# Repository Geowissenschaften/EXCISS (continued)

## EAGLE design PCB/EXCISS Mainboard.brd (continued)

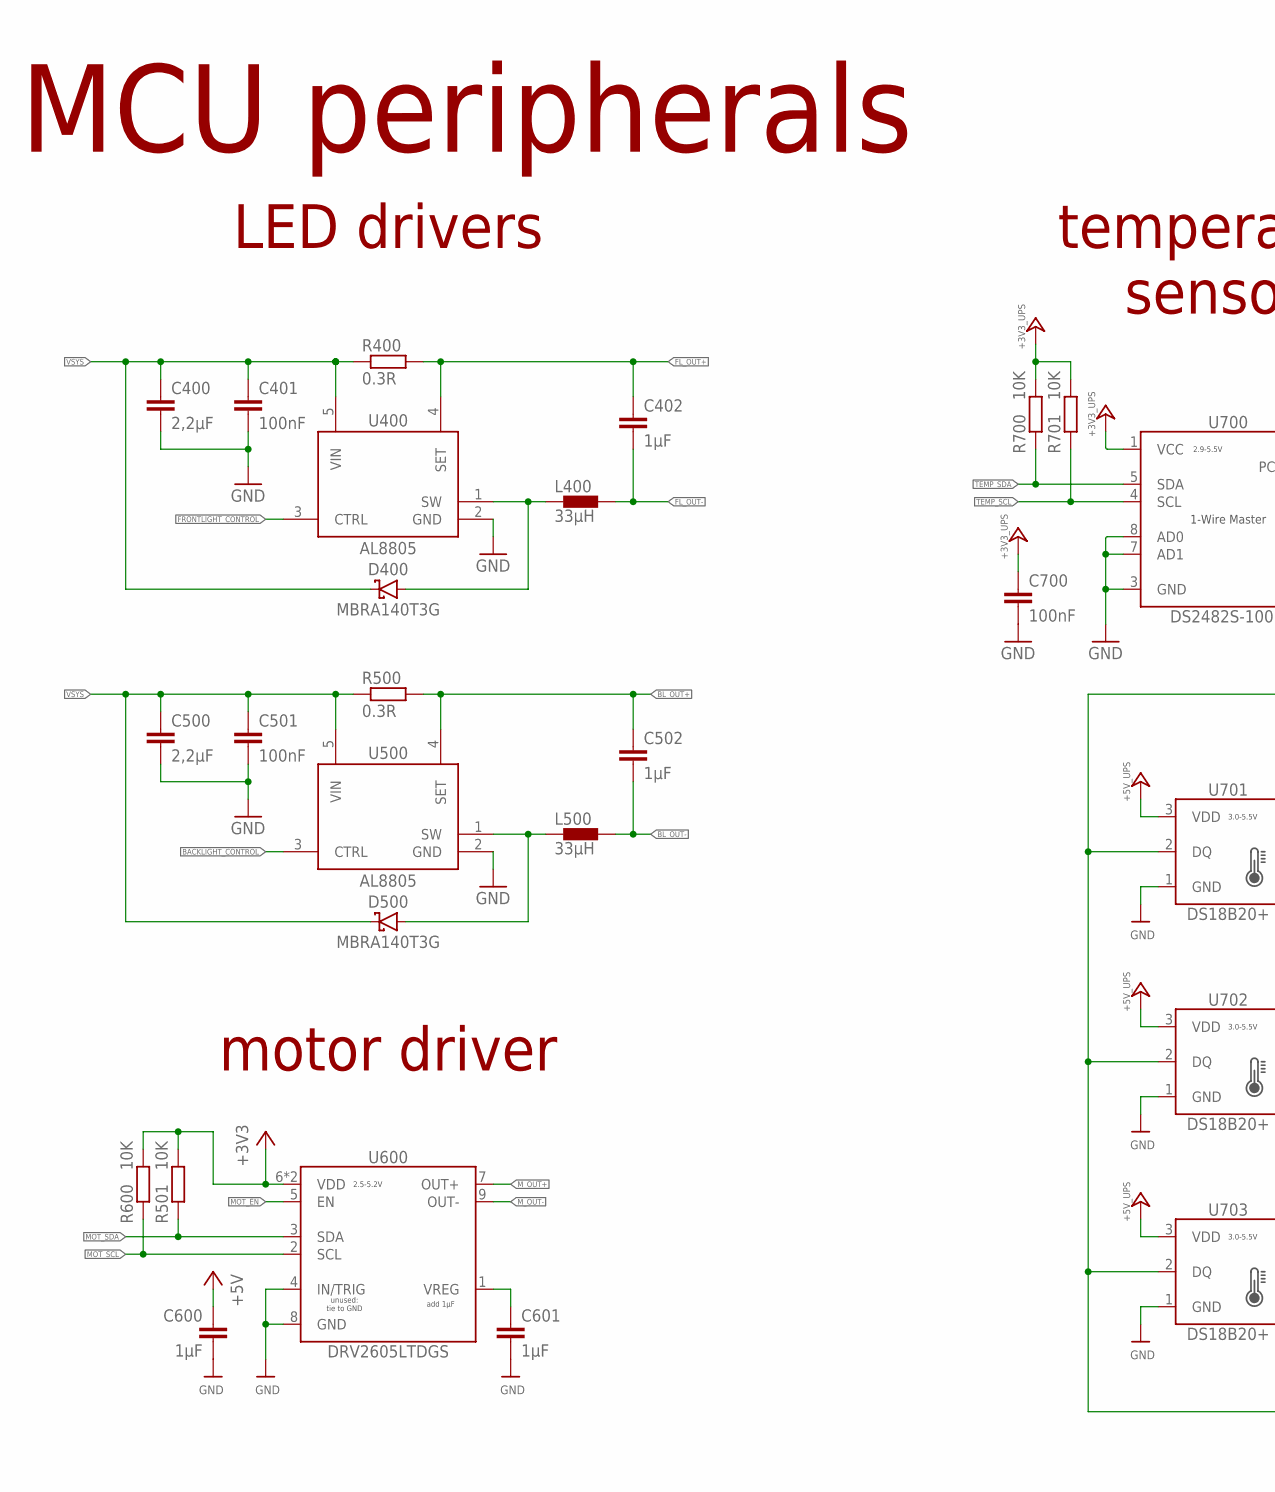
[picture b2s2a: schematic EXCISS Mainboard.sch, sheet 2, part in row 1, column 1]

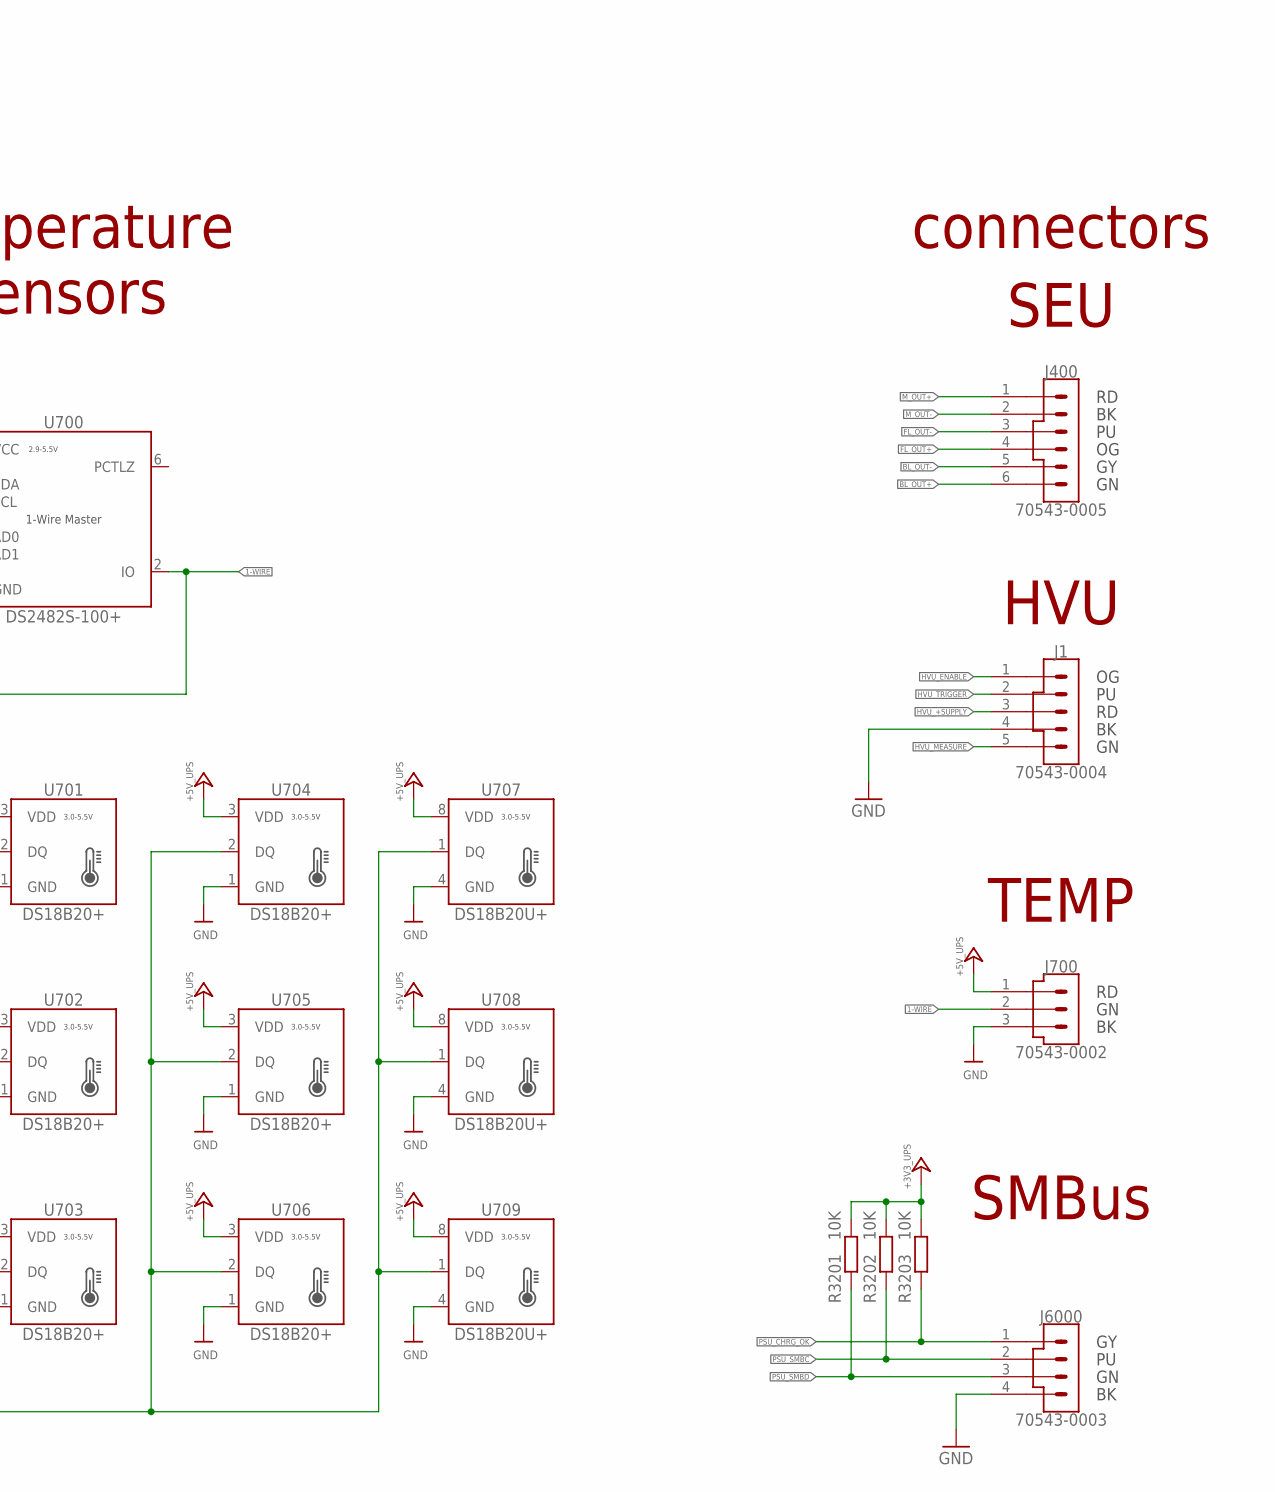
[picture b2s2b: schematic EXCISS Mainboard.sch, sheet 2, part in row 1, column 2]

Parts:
C400, C500: 2,2µF; C1206
C401, C501: 100nF; C0805
C402, C502, C600, C601: 1µF; C0805
C700: 100nF; C0603
D400, D500: MBRA140T3G; 403D-02
J1: 70543-0004; MOLEX_70543-0004
J400: 70543-0005; MOLEX_70543-0005
J700: 70543-0002; MOLEX_70543-0002
J6000: 70543-0003; MOLEX_70543-0003
L400, L500: 33µH; SRN6045
R400, R500: 0.3R; R0805
R501, R600, R700, R701, R3201, R3202, R3203: 10K; R0603
U400, U500: AL8805; DBV(R-PDSO-G5)
U600: DRV2605LTDGS; PSOP10
U700: DS2482S-100+; SOIC8
U701, U702, U703, U704, U705, U706: DS18B20+; TO-92-STRAIGHT
U707, U708, U709: DS18B20U+; µSOP

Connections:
1-WIRE: J700.2, U700.2 (IO), U701.2 (DQ), U702.2 (DQ), U703.2 (DQ), U704.2 (DQ), U705.2 (DQ), U706.2 (DQ), U707.1 (DQ), U708.1 (DQ), U709.1 (DQ)
+3V3: C600.1, R501.1, R600.1, U600.6 (VDD), U600.10 (VDD); also elsewhere on the board
+3V3_UPS: C700.1, R700.1, R701.1, R3201.1, R3202.1, R3203.1, U700.1 (VCC); also elsewhere on the board
+5V_UPS: J700.1, U701.3 (VDD), U702.3 (VDD), U703.3 (VDD), U704.3 (VDD), U705.3 (VDD), U706.3 (VDD), U707.8 (VDD), U708.8 (VDD), U709.8 (VDD); also elsewhere on the board
BACKLIGHT_CONTROL: U500.3 (CTRL); also elsewhere on the board
BL_OUT+: C502.1, J400.6, R500.2, U500.4 (SET)
BL_OUT-: C502.2, J400.5, L500.2
BL_SW: D500.A, L500.1, U500.1 (SW)
FL_OUT+: C402.1, J400.4, R400.2, U400.4 (SET)
FL_OUT-: C402.2, J400.3, L400.2
FL_SW: D400.A, L400.1, U400.1 (SW)
FRONTLIGHT_CONTROL: U400.3 (CTRL); also elsewhere on the board
GND: C400.2, C401.2, C500.2, C501.2, C600.2, C601.2, C700.2, J1.4, J700.3, J6000.4, U400.2 (GND), U500.2 (GND), U600.4 (IN/TRIG), U600.8 (GND), U700.3 (GND), U700.7 (AD1), U700.8 (AD0), U701.1 (GND), U702.1 (GND), U703.1 (GND), U704.1 (GND), U705.1 (GND), U706.1 (GND), U707.4 (GND), U708.4 (GND), U709.4 (GND); also elsewhere on the board
HVU_+SUPPLY: J1.3; also elsewhere on the board
HVU_ENABLE: J1.1; also elsewhere on the board
HVU_MEASURE: J1.5; also elsewhere on the board
HVU_TRIGGER: J1.2; also elsewhere on the board
MOT_!EN: U600.5 (EN); also elsewhere on the board
MOT_SCL: R600.2, U600.2 (SCL); also elsewhere on the board
MOT_SDA: R501.2, U600.3 (SDA); also elsewhere on the board
M_OUT+: J400.1, U600.7 (OUT+)
M_OUT-: J400.2, U600.9 (OUT-)
unnamed: C601.1, U600.1 (VREG)
PSU_CHRG_OK: J6000.1, R3203.2; also elsewhere on the board
PSU_SMBC: J6000.2, R3202.2; also elsewhere on the board
PSU_SMBD: J6000.3, R3201.2; also elsewhere on the board
TEMP_SCL: R701.2, U700.4 (SCL); also elsewhere on the board
TEMP_SDA: R700.2, U700.5 (SDA); also elsewhere on the board
VSYS: C400.1, C401.1, C500.1, C501.1, D400.C, D500.C, R400.1, R500.1, U400.5 (VIN), U500.5 (VIN); also elsewhere on the board

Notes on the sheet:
MCU peripherals
LED drivers
motor driver
temperature sensors
connectors
SEU
TEMP
HVU
SMBus

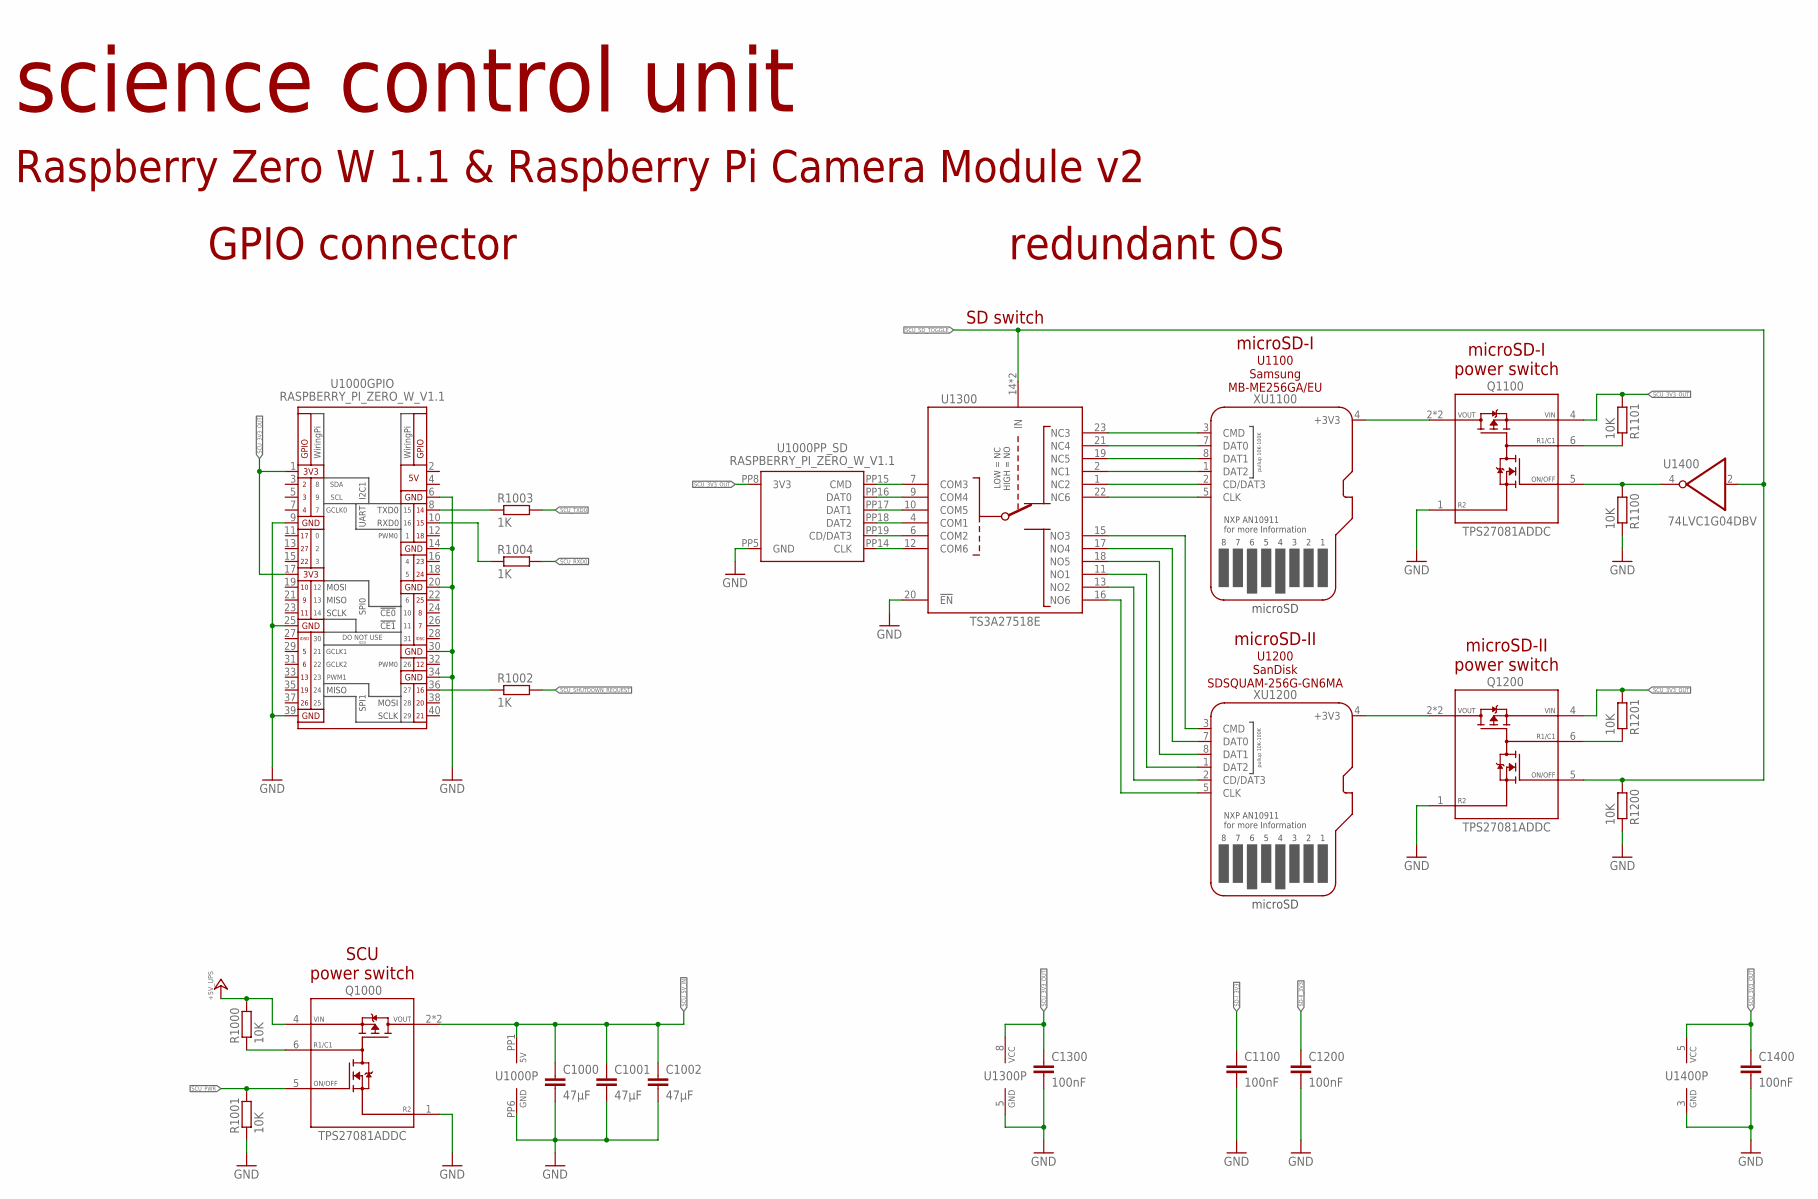
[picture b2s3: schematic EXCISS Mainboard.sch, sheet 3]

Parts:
C1000, C1001, C1002: 47µF; C1210
C1100, C1200, C1300, C1400: 100nF; C0603
Q1000, Q1100, Q1200: TPS27081ADDC; DDC(R-PDSO-G6)
R1000, R1001, R1100, R1101, R1200, R1201: 10K; R0603
R1002, R1003, R1004: 1K; R0603
U1000: RASPBERRY_PI_ZERO_W_V1.1
U1300: TS3A27518E; TSSOP24
U1400: 74LVC1G04DBV; DBV(R-PDSO-G5)
XU1100, XU1200: MICROSDMOLEX_104031; MICROSD_MOLEX_104031

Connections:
+5V_UPS: Q1000.4 (VIN), R1000.2; also elsewhere on the board
GND: C1000.2, C1001.2, C1002.2, C1100.2, C1200.2, C1300.2, C1400.2, Q1000.1 (R2), Q1100.1 (R2), Q1200.1 (R2), R1001.1, R1100.1, R1200.1, U1000.6 (GND), U1000.9 (GND), U1000.14 (GND), U1000.20 (GND), U1000.25 (GND), U1000.30 (GND), U1000.34 (GND), U1000.39 (GND), U1000.PP5 (GND), U1000.PP6 (GND), U1300.5 (GND), U1300.20 (!EN), U1400.3 (GND), XU1100.6 (GND), XU1100.G1 (GND), XU1100.G2 (GND), XU1100.G3 (GND), XU1100.G4 (GND), XU1200.6 (GND), XU1200.G1 (GND), XU1200.G2 (GND), XU1200.G3 (GND), XU1200.G4 (GND); also elsewhere on the board
unnamed: U1000.PP15 (CMD), U1300.7 (COM3)
unnamed: U1000.PP16 (DAT0), U1300.9 (COM4)
unnamed: U1000.PP14 (CLK), U1300.12 (COM6)
unnamed: U1000.PP19 (CD/DAT3), U1300.6 (COM2)
unnamed: U1000.PP18 (DAT2), U1300.4 (COM1)
unnamed: U1000.PP17 (DAT1), U1300.10 (COM5)
unnamed: R1002.1, U1000.36 (GPIO16)
unnamed: R1004.1, U1000.10 (GPIO15/RXD0)
unnamed: R1003.1, U1000.8 (GPIO14/TXD0)
R1/C1: Q1100.6 (R1/C1), R1101.1
R1/C2: Q1200.6 (R1/C1), R1201.1
R1/C6: Q1000.6 (R1/C1), R1000.1
SCU_3V3_OUT: C1300.1, C1400.1, Q1100.4 (VIN), Q1200.4 (VIN), R1101.2, R1201.2, U1000.1 (3V3), U1000.17 (3V3), U1000.PP8 (3V3), U1300.8 (VCC), U1400.5 (VCC)
SCU_5V_IN: C1000.1, C1001.1, C1002.1, Q1000.2 (VOUT), Q1000.3 (VOUT), U1000.PP1 (5V)
SCU_PWR: Q1000.5 (ON/OFF), R1001.2; also elsewhere on the board
SCU_RXD0: R1004.2; also elsewhere on the board
SCU_SD_!TOGGLE: Q1100.5 (ON/OFF), R1100.2, U1400.4 (O)
SCU_SD_TOGGLE: Q1200.5 (ON/OFF), R1200.2, U1300.14 (IN), U1300.24 (IN), U1400.2 (I); also elsewhere on the board
SCU_SHUTDOWN_REQUEST: R1002.2; also elsewhere on the board
SCU_TXD0: R1003.2; also elsewhere on the board
SD-1_CD/DAT3: U1300.1 (NC2), XU1100.2 (CD/DAT3)
SD-1_CLK: U1300.22 (NC6), XU1100.5 (CLK)
SD-1_CMD: U1300.23 (NC3), XU1100.3 (CMD)
SD-1_DAT0: U1300.21 (NC4), XU1100.7 (DAT0)
SD-1_DAT1: U1300.19 (NC5), XU1100.8 (DAT1)
SD-1_DAT2: U1300.2 (NC1), XU1100.1 (DAT2)
SD-2_CD/DAT3: U1300.13 (NO2), XU1200.2 (CD/DAT3)
SD-2_CLK: U1300.16 (NO6), XU1200.5 (CLK)
SD-2_CMD: U1300.15 (NO3), XU1200.3 (CMD)
SD-2_DAT0: U1300.17 (NO4), XU1200.7 (DAT0)
SD-2_DAT1: U1300.18 (NO5), XU1200.8 (DAT1)
SD-2_DAT2: U1300.11 (NO1), XU1200.1 (DAT2)
SD-II_3V3: C1200.1, Q1200.2 (VOUT), Q1200.3 (VOUT), XU1200.4 (+3V3)
SD-I_3V3: C1100.1, Q1100.2 (VOUT), Q1100.3 (VOUT), XU1100.4 (+3V3)

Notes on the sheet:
science control unit
GPIO connector
redundant OS
microSD-I power switch
microSD-II power switch
SCU power switch
Raspberry Zero W 1.1 & Raspberry Pi Camera Module v2
microSD-I
microSD-II
SD switch
U1100 Samsung MB-ME256GA/EU
U1200 SanDisk SDSQUAM-256G-GN6MA

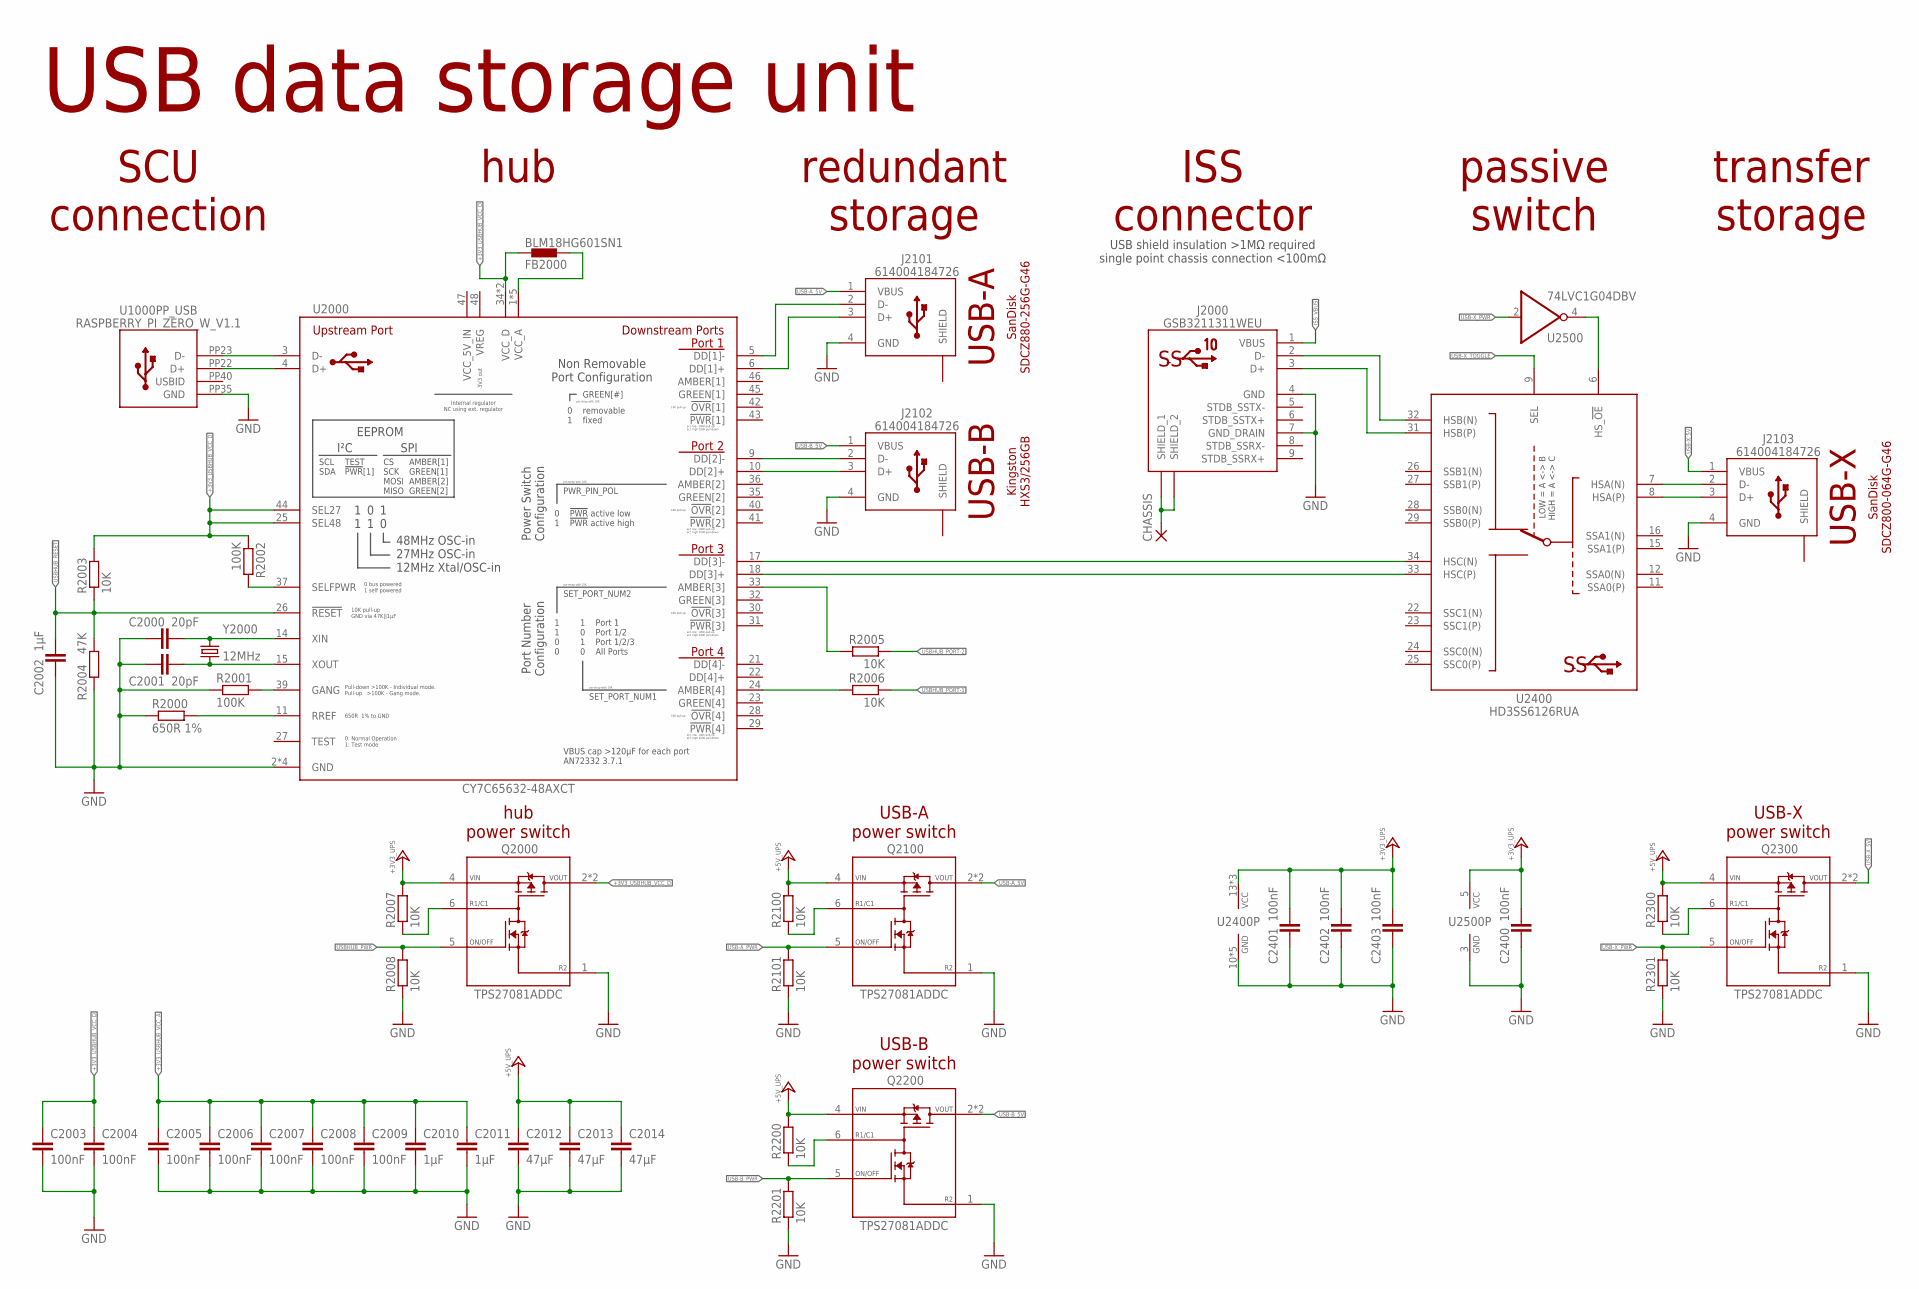
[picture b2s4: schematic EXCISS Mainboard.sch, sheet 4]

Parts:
C2000, C2001: 20pF; C0603
C2002, C2010, C2011: 1µF; C0805
C2003, C2004, C2005, C2006, C2007, C2008, C2009, C2400, C2401, C2402, C2403: 100nF; C0603
C2012, C2013, C2014: 47µF; C1210
CHASSIS: PAD_M2.5
FB2000: BLM18HG601SN1; 0603
J2000: GSB3211311WEU
J2101, J2102, J2103: 614004184726
Q2000, Q2100, Q2200, Q2300: TPS27081ADDC; DDC(R-PDSO-G6)
R2000: 650R 1%; R0603
R2001, R2002: 100K; R0603
R2003, R2005, R2006, R2007, R2008, R2100, R2101, R2200, R2201, R2300, R2301: 10K; R0603
R2004: 47K; R0603
U1000: RASPBERRY_PI_ZERO_W_V1.1
U2000: CY7C65632-48AXCT; TQFP48
U2400: HD3SS6126RUA; RUA(R-PWQFN-N42)
U2500: 74LVC1G04DBV; DBV(R-PDSO-G5)
Y2000: 12MHz; HC49UP

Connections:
+3V3_UPS: C2400.1, C2401.1, C2402.1, C2403.1, Q2000.4 (VIN), R2007.2, U2400.13 (VCC), U2400.20 (VCC), U2400.30 (VCC), U2500.5 (VCC); also elsewhere on the board
+3V3_USBHUB_VCC_A: C2005.1, C2006.1, C2007.1, C2008.1, C2009.1, C2010.1, C2011.1, FB2000.2, U2000.1 (VCC_A), U2000.7 (VCC_A), U2000.12 (VCC_A), U2000.16 (VCC_A), U2000.19 (VCC_A)
+3V3_USBHUB_VCC_D: C2003.1, C2004.1, FB2000.1, Q2000.2 (VOUT), Q2000.3 (VOUT), R2002.1, R2003.2, U2000.25 (SEL48), U2000.34 (VCC_D), U2000.38 (VCC_D), U2000.44 (SEL27)
+5V_UPS: C2012.1, C2013.1, C2014.1, Q2100.4 (VIN), Q2200.4 (VIN), Q2300.4 (VIN), R2100.2, R2200.2, R2300.2; also elsewhere on the board
DD[1]_N: J2101.2 (D-), U2000.5 (DD[1]-)
DD[1]_P: J2101.3 (D+), U2000.6 (DD[1]+)
DD[2]_N: J2102.2 (D-), U2000.9 (DD[2]-)
DD[2]_P: J2102.3 (D+), U2000.10 (DD[2]+)
DD[3]_N: U2000.17 (DD[3]-), U2400.34 (HSC(N))
DD[3]_P: U2000.18 (DD[3]+), U2400.33 (HSC(P))
DU_N: U1000.PP23 (D-), U2000.3 (D-)
DU_P: U1000.PP22 (D+), U2000.4 (D+)
GND: C2000.2, C2001.2, C2002.2, C2003.2, C2004.2, C2005.2, C2006.2, C2007.2, C2008.2, C2009.2, C2010.2, C2011.2, C2012.2, C2013.2, C2014.2, C2400.2, C2401.2, C2402.2, C2403.2, J2000.4 (GND), J2000.7 (GND_DRAIN), J2101.4 (GND), J2102.4 (GND), J2103.4 (GND), Q2000.1 (R2), Q2100.1 (R2), Q2200.1 (R2), Q2300.1 (R2), R2000.1, R2001.1, R2004.1, R2008.1, R2101.1, R2201.1, R2301.1, U1000.PP35 (GND), U2000.2 (GND), U2000.8 (GND), U2000.13 (GND), U2000.20 (GND), U2400.10 (GND), U2400.14 (GND), U2400.17 (GND), U2400.19 (GND), U2400.21 (GND), U2400.TP0 (GND), U2400.TP1 (GND), U2400.TP2 (GND), U2400.TP3 (GND), U2400.TP4 (GND), U2400.TP5 (GND), U2400.TP6 (GND), U2400.TP7 (GND), U2400.TP8 (GND), U2400.TP9 (GND), U2400.TP10 (GND), U2400.TP11 (GND), U2400.TP12 (GND), U2400.TP13 (GND), U2400.TP14 (GND), U2500.3 (GND); also elsewhere on the board
ISS_VBUS: J2000.1 (VBUS); also elsewhere on the board
unnamed: CHASSIS.P$1, J2000.SHIELD_1, J2000.SHIELD_2
unnamed: Q2100.6 (R1/C1), R2100.1
unnamed: R2001.2, U2000.39 (GANG)
unnamed: C2000.1, U2000.14 (XIN), Y2000.1
unnamed: C2001.1, U2000.15 (XOUT), Y2000.2
unnamed: R2006.2, U2000.24 (AMBER[4])
unnamed: R2005.2, U2000.33 (AMBER[3])
unnamed: R2000.2, U2000.11 (RREF)
unnamed: R2002.2, U2000.37 (SELFPWR)
R1/C3: Q2000.6 (R1/C1), R2007.1
R1/C4: Q2200.6 (R1/C1), R2200.1
R1/C5: Q2300.6 (R1/C1), R2300.1
USB-A_5V: J2101.1 (VBUS), Q2100.2 (VOUT), Q2100.3 (VOUT)
USB-A_PWR: Q2100.5 (ON/OFF), R2101.2; also elsewhere on the board
USB-B_5V: J2102.1 (VBUS), Q2200.2 (VOUT), Q2200.3 (VOUT)
USB-B_PWR: Q2200.5 (ON/OFF), R2201.2; also elsewhere on the board
USB-X_5V: J2103.1 (VBUS), Q2300.2 (VOUT), Q2300.3 (VOUT)
USB-X_!PWR: U2400.6 (HS_!OE), U2500.4 (O)
USB-X_PWR: Q2300.5 (ON/OFF), R2301.2, U2500.2 (I); also elsewhere on the board
USB-X_TOGGLE: U2400.9 (SEL); also elsewhere on the board
USBHUB_!RESET: C2002.1, R2003.1, R2004.2, U2000.26 (!RESET); also elsewhere on the board
USBHUB_PORT-1: R2006.1; also elsewhere on the board
USBHUB_PORT-2: R2005.1; also elsewhere on the board
USBHUB_PWR: Q2000.5 (ON/OFF), R2008.2; also elsewhere on the board
USBISS_D_N: J2000.2 (D-), U2400.32 (HSB(N))
USBISS_D_P: J2000.3 (D+), U2400.31 (HSB(P))
USBX_D_N: J2103.2 (D-), U2400.7 (HSA(N))
USBX_D_P: J2103.3 (D+), U2400.8 (HSA(P))
VCC_5V_IN: U2000.47 (VCC_5V_IN)

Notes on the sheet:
USB data storage unit
hub
passive switch
USB-X
USB-A
USB-B
ISS connector
redundant storage
SCU connection
transfer storage
USB shield insulation >1MΩ required single point chassis connection <100mΩ
SanDisk SDCZ880-256G-G46
Kingston HXS3/256GB
SanDisk SDCZ800-064G-G46
USB-A power switch
USB-B power switch
hub power switch
USB-X power switch

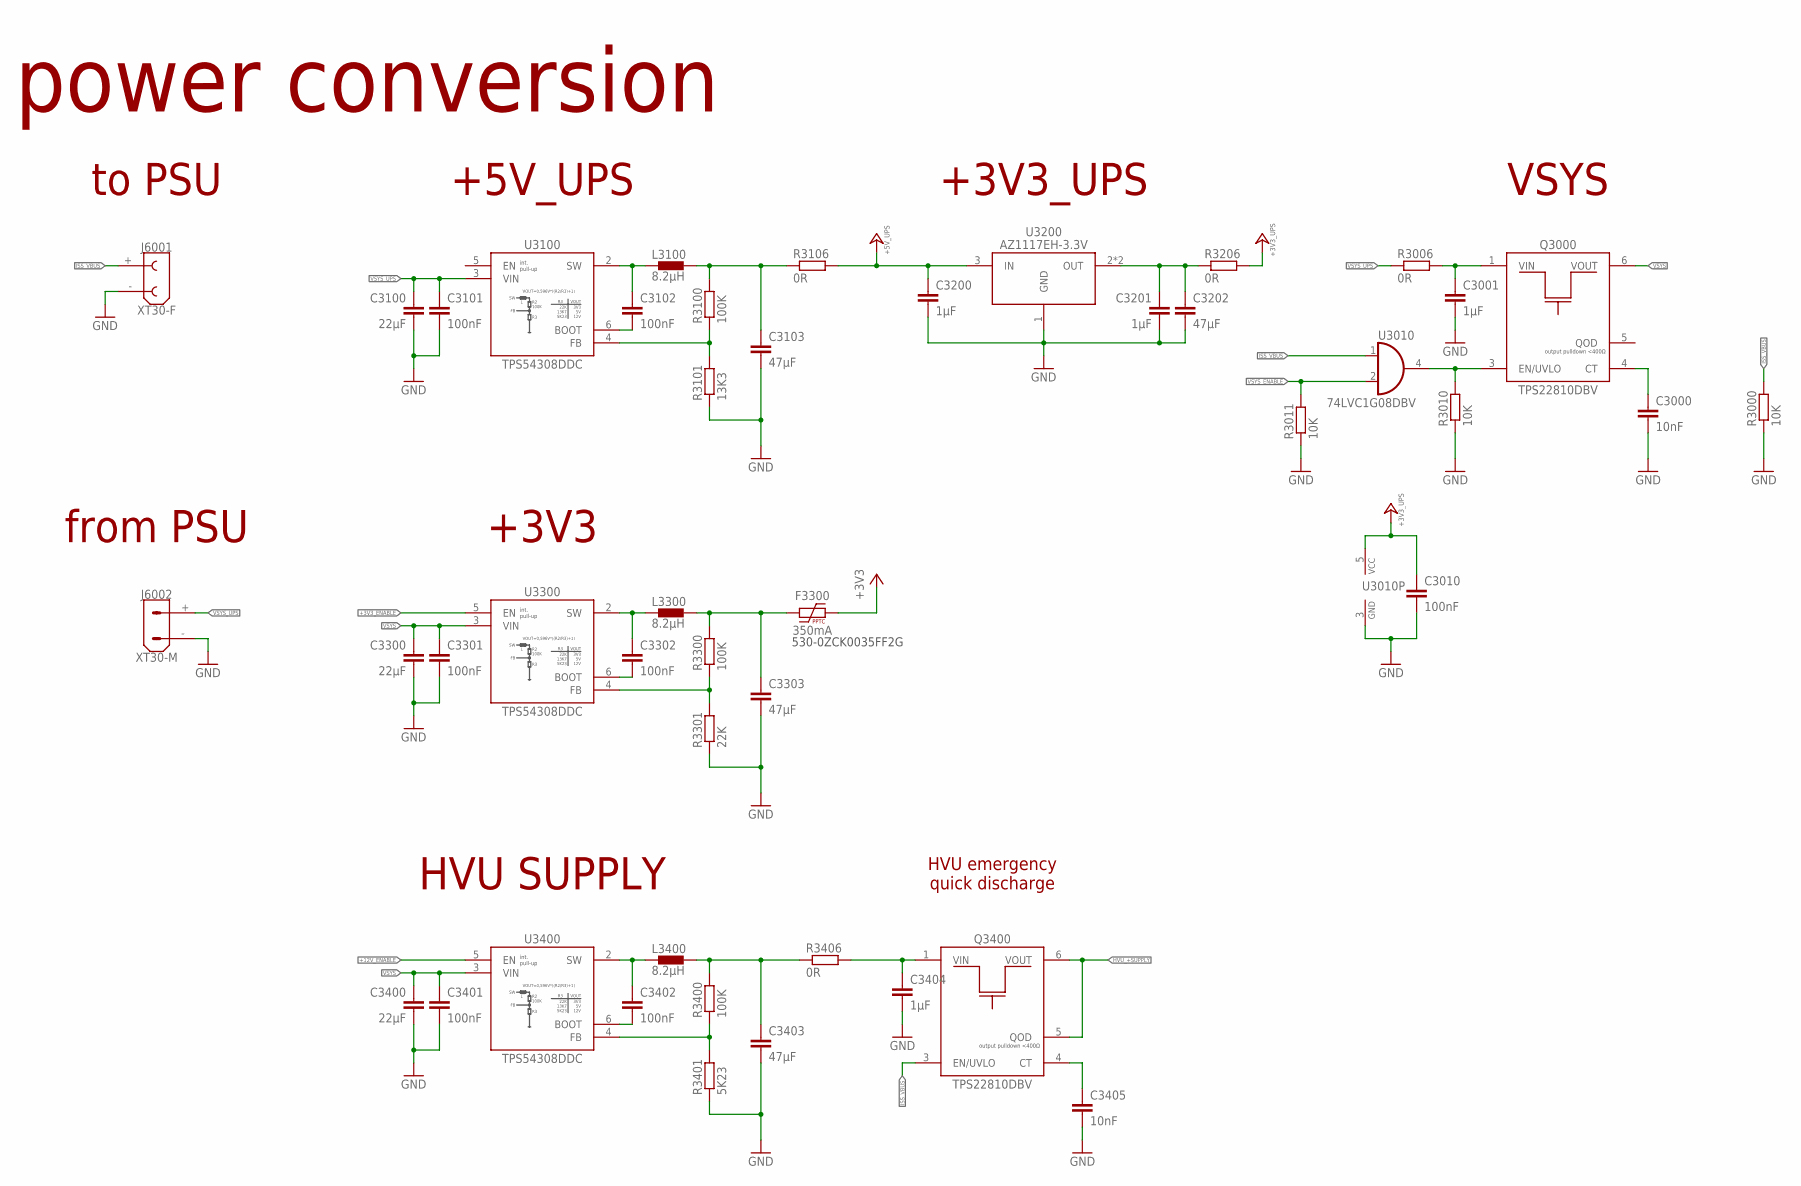
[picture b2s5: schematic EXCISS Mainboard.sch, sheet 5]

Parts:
C3000, C3405: 10nF; C0603
C3001, C3200, C3201, C3404: 1µF; C0805
C3010, C3101, C3102, C3301, C3302, C3401, C3402: 100nF; C0805
C3100, C3300, C3400: 22µF; C1206
C3103, C3202, C3303, C3403: 47µF; C1210
F3300: 350mA; R0805_NOCREAM
J6001: XT30-F
J6002: XT30-M
L3100, L3300, L3400: 8.2µH; SRP6540
Q3000, Q3400: TPS22810DBV; SOT23-6_DBV
R3000: 10K; R1206
R3006, R3106, R3206, R3406: 0R; R0805_NOCREAM
R3010, R3011: 10K; R0603
R3100, R3300, R3400: 100K; R0603
R3101: 13K3; R0603
R3301: 22K; R0603
R3401: 5K23; R0603
U3010: 74LVC1G08DBV; SOT23-5
U3100, U3300, U3400: TPS54308DDC; DDC(R-PDSO-G6)
U3200: AZ1117EH-3.3V; SOT223

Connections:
+3V3: F3300.2; also elsewhere on the board
+3V3_ENABLE: U3300.5 (EN); also elsewhere on the board
+3V3_UPS: C3010.1, R3206.2, U3010.5 (VCC); also elsewhere on the board
+5V_UPS: C3200.1, R3106.2, U3200.3 (IN); also elsewhere on the board
+12V_ENABLE: U3400.5 (EN); also elsewhere on the board
+12V_STEPDOWN: C3403.1, L3400.2, R3400.2, R3406.1
BST_+5V: C3302.2, U3300.6 (BOOT)
BST_+5V_UPS: C3102.2, U3100.6 (BOOT)
BST_+12V: C3402.2, U3400.6 (BOOT)
GND: C3000.2, C3001.2, C3010.2, C3100.2, C3101.2, C3103.2, C3200.2, C3201.2, C3202.2, C3300.2, C3301.2, C3303.2, C3400.2, C3401.2, C3403.2, C3404.2, C3405.2, J6001.-, J6002.-, Q3000.2 (GND), Q3400.2 (GND), R3000.1, R3010.1, R3011.1, R3101.1, R3301.1, R3401.1, U3010.3 (GND), U3100.1 (GND), U3200.1 (GND), U3300.1 (GND), U3400.1 (GND); also elsewhere on the board
HVU_+SUPPLY: Q3400.5 (QOD), Q3400.6 (VOUT); also elsewhere on the board
ISS_VBUS: J6001.+, Q3400.3 (EN/UVLO), R3000.2, U3010.1 (I0); also elsewhere on the board
unnamed: C3405.1, Q3400.4 (CT)
unnamed: C3000.1, Q3000.4 (CT)
unnamed: C3103.1, L3100.2, R3100.2, R3106.1
unnamed: C3303.1, F3300.1, L3300.2, R3300.2
unnamed: C3404.1, Q3400.1 (VIN), R3406.2
unnamed: C3001.1, Q3000.1 (VIN), R3006.2
unnamed: Q3000.3 (EN/UVLO), R3010.2, U3010.4 (O)
OUT: C3201.1, C3202.1, R3206.1, U3200.2 (OUT), U3200.4 (OUT)
SW_+5V: C3302.1, L3300.1, U3300.2 (SW)
SW_+5V_UPS: C3102.1, L3100.1, U3100.2 (SW)
SW_+12V: C3402.1, L3400.1, U3400.2 (SW)
VFB_+5V: R3300.1, R3301.2, U3300.4 (FB)
VFB_+5V_UPS: R3100.1, R3101.2, U3100.4 (FB)
VFB_+12V: R3400.1, R3401.2, U3400.4 (FB)
VSYS: C3300.1, C3301.1, C3400.1, C3401.1, Q3000.6 (VOUT), U3300.3 (VIN), U3400.3 (VIN); also elsewhere on the board
VSYS_ENABLE: R3011.2, U3010.2 (I1); also elsewhere on the board
VSYS_UPS: C3100.1, C3101.1, J6002.+, R3006.1, U3100.3 (VIN)

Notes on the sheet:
power conversion
VSYS
+5V_UPS
+3V3_UPS
+3V3
HVU SUPPLY
HVU emergency quick discharge
to PSU
from PSU
530-0ZCK0035FF2G

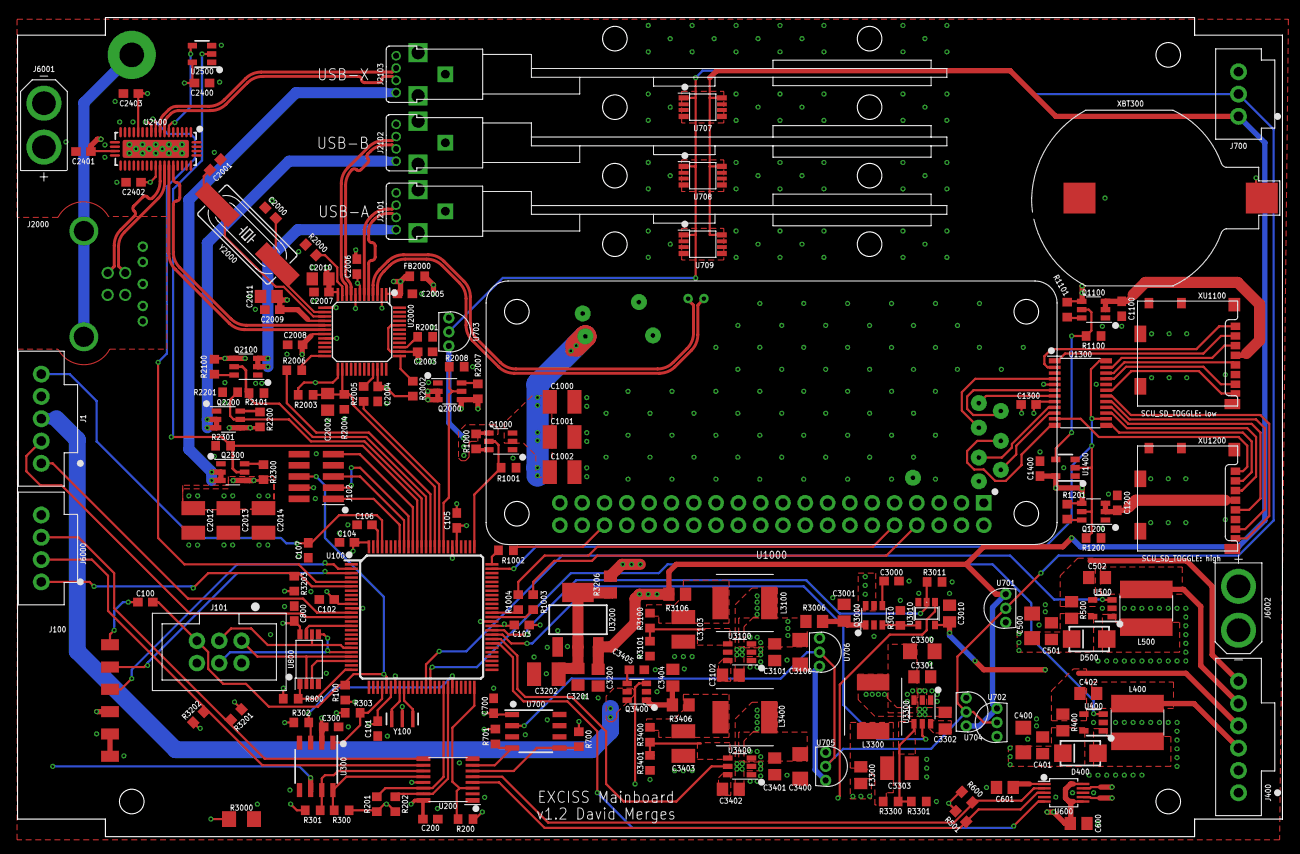
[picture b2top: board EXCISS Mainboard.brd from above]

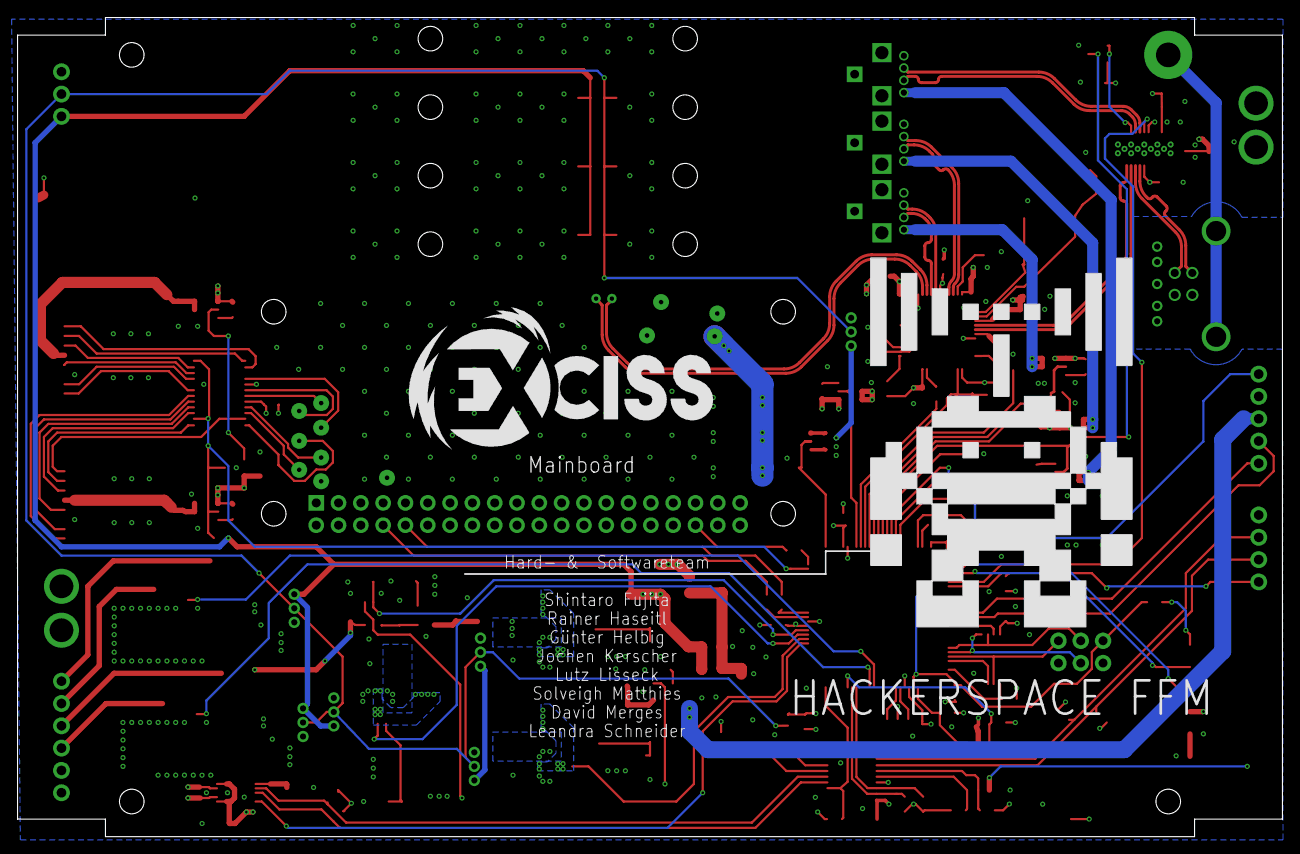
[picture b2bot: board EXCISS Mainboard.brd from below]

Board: 4 copper layers, 144.0 x 93.2 mm, 194 parts (2 on the bottom side), 149 nets.

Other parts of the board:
U$1: KINGSTON_USB_TRIPLE
U$3: NANOLAB_1.5U
U$4: NANOLAB_1.5U_LIDS
U$15: LOGO_EXCISS
U$16, U$17, U$18: DRILL_M2.5
U$19: LOGO_HACKFFM
